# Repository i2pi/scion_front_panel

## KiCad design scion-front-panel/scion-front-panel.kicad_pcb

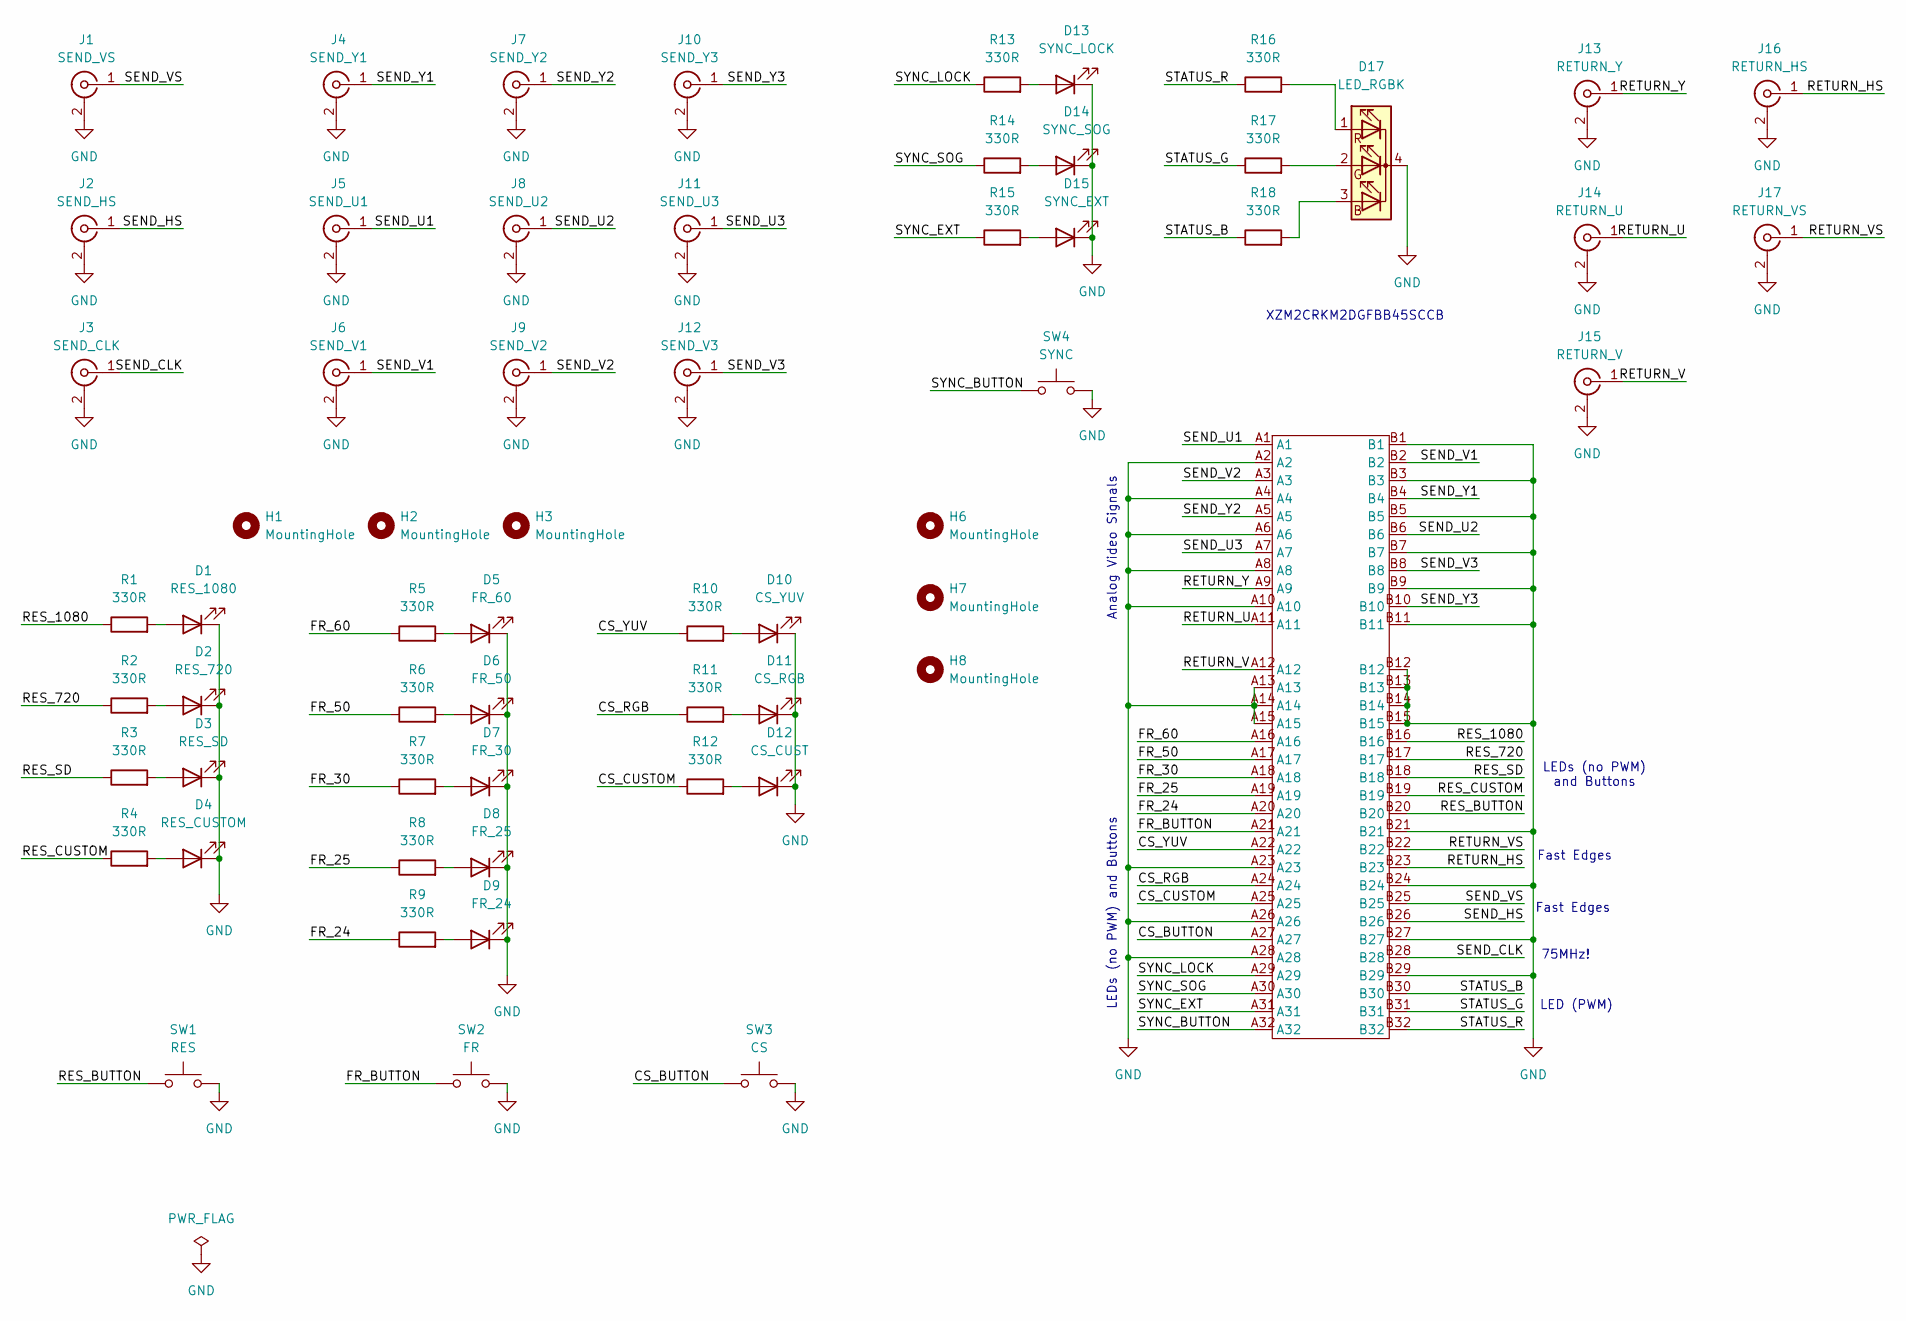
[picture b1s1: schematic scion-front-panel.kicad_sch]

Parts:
D1: RES_1080; LED_0805_2012Metric
D2: RES_720; LED_0805_2012Metric
D3: RES_SD; LED_0805_2012Metric
D4: RES_CUSTOM; LED_0805_2012Metric
D5: FR_60; LED_0805_2012Metric
D6: FR_50; LED_0805_2012Metric
D7: FR_30; LED_0805_2012Metric
D8: FR_25; LED_0805_2012Metric
D9: FR_24; LED_0805_2012Metric
D10: CS_YUV; LED_0805_2012Metric
D11: CS_RGB; LED_0805_2012Metric
D12: CS_CUST; LED_0805_2012Metric
D13: SYNC_LOCK; LED_0805_2012Metric
D14: SYNC_SOG; LED_0805_2012Metric
D15: SYNC_EXT; LED_0805_2012Metric
D17: LED_RGBK; LED_RGB_Wuerth-PLCC4_3.2x2.8mm_150141M173100
H1, H2, H3, H6, H7, H8: MountingHole; MountingHole_2.2mm_M2
J1: SEND_VS; SAMTEC_DIN7A-J-P-GF-ST-TH1
J2: SEND_HS; SAMTEC_DIN7A-J-P-GF-ST-TH1
J3: SEND_CLK; SAMTEC_DIN7A-J-P-GF-ST-TH1
J4: SEND_Y1; SAMTEC_DIN7A-J-P-GF-ST-TH1
J5: SEND_U1; SAMTEC_DIN7A-J-P-GF-ST-TH1
J6: SEND_V1; SAMTEC_DIN7A-J-P-GF-ST-TH1
J7: SEND_Y2; SAMTEC_DIN7A-J-P-GF-ST-TH1
J8: SEND_U2; SAMTEC_DIN7A-J-P-GF-ST-TH1
J9: SEND_V2; SAMTEC_DIN7A-J-P-GF-ST-TH1
J10: SEND_Y3; SAMTEC_DIN7A-J-P-GF-ST-TH1
J11: SEND_U3; SAMTEC_DIN7A-J-P-GF-ST-TH1
J12: SEND_V3; SAMTEC_DIN7A-J-P-GF-ST-TH1
J13: RETURN_Y; SAMTEC_DIN7A-J-P-GF-ST-TH1
J14: RETURN_U; SAMTEC_DIN7A-J-P-GF-ST-TH1
J15: RETURN_V; SAMTEC_DIN7A-J-P-GF-ST-TH1
J16: RETURN_HS; SAMTEC_DIN7A-J-P-GF-ST-TH1
J17: RETURN_VS; SAMTEC_DIN7A-J-P-GF-ST-TH1
J18: Bus_PCI_Express_x4-SCION; BUS_PCIexpress_x4
R1, R2, R3, R4, R5, R6, R7, R8, R9, R10, R11, R12, R13, R14, R15, R16, R17, R18: 330R; R_0402_1005Metric
SW1: RES; SW_SPST_Omron_B3FS-105xP
SW2: FR; SW_SPST_Omron_B3FS-105xP
SW3: CS; SW_SPST_Omron_B3FS-105xP
SW4: SYNC; SW_SPST_Omron_B3FS-105xP

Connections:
/CS_BUTTON: J18.A27, SW3.1
/CS_CUSTOM: J18.A25, R12.1
/CS_RGB: J18.A24, R11.1
/CS_YUV: J18.A22, R10.1
/FR_24: J18.A20, R9.1
/FR_25: J18.A19, R8.1
/FR_30: J18.A18, R7.1
/FR_50: J18.A17, R6.1
/FR_60: J18.A16, R5.1
/FR_BUTTON: J18.A21, SW2.1
/RES_720: J18.B17, R2.1
/RES_1080: J18.B16, R1.1
/RES_BUTTON: J18.B20, SW1.1
/RES_CUSTOM: J18.B19, R4.1
/RES_SD: J18.B18, R3.1
/RETURN_HS: J16.1 (In), J18.B23
/RETURN_U: J14.1 (In), J18.A11
/RETURN_V: J15.1 (In), J18.A12
/RETURN_VS: J17.1 (In), J18.B22
/RETURN_Y: J13.1 (In), J18.A9
/SEND_CLK: J3.1 (In), J18.B28
/SEND_HS: J2.1 (In), J18.B26
/SEND_U1: J5.1 (In), J18.A1
/SEND_U2: J8.1 (In), J18.B6
/SEND_U3: J11.1 (In), J18.A7
/SEND_V1: J6.1 (In), J18.B2
/SEND_V2: J9.1 (In), J18.A3
/SEND_V3: J12.1 (In), J18.B8
/SEND_VS: J1.1 (In), J18.B25
/SEND_Y1: J4.1 (In), J18.B4
/SEND_Y2: J7.1 (In), J18.A5
/SEND_Y3: J10.1 (In), J18.B10
/STATUS_B: J18.B30, R18.1
/STATUS_G: J18.B31, R17.1
/STATUS_R: J18.B32, R16.1
/SYNC_BUTTON: J18.A32, SW4.1
/SYNC_EXT: J18.A31, R15.1
/SYNC_LOCK: J18.A29, R13.1
/SYNC_SOG: J18.A30, R14.1
GND: D1.1 (K), D2.1 (K), D3.1 (K), D4.1 (K), D5.1 (K), D6.1 (K), D7.1 (K), D8.1 (K), D9.1 (K), D10.1 (K), D11.1 (K), D12.1 (K), D13.1 (K), D14.1 (K), D15.1 (K), D17.4 (K), J1.2 (Ext), J2.2 (Ext), J3.2 (Ext), J4.2 (Ext), J5.2 (Ext), J6.2 (Ext), J7.2 (Ext), J8.2 (Ext), J9.2 (Ext), J10.2 (Ext), J11.2 (Ext), J12.2 (Ext), J13.2 (Ext), J14.2 (Ext), J15.2 (Ext), J16.2 (Ext), J17.2 (Ext), J18.A2, J18.A4, J18.A6, J18.A8, J18.A10, J18.A13, J18.A14, J18.A15, J18.A23, J18.A26, J18.A28, J18.B1, J18.B3, J18.B5, J18.B7, J18.B9, J18.B11, J18.B12, J18.B13, J18.B14, J18.B15, J18.B21, J18.B24, J18.B27, J18.B29, SW1.2, SW2.2, SW3.2, SW4.2
unnamed: D1.2 (A), R1.2
unnamed: D2.2 (A), R2.2
unnamed: D3.2 (A), R3.2
unnamed: D4.2 (A), R4.2
unnamed: D5.2 (A), R5.2
unnamed: D6.2 (A), R6.2
unnamed: D7.2 (A), R7.2
unnamed: D8.2 (A), R8.2
unnamed: D9.2 (A), R9.2
unnamed: D10.2 (A), R10.2
unnamed: D11.2 (A), R11.2
unnamed: D12.2 (A), R12.2
unnamed: D13.2 (A), R13.2
unnamed: D14.2 (A), R14.2
unnamed: D15.2 (A), R15.2
unnamed: D17.3 (BA), R18.2
unnamed: D17.2 (GA), R17.2
unnamed: D17.1 (RA), R16.2

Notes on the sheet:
75MHz!
Analog Video Signals
LEDs (no PWM) and Buttons
LED (PWM)
XZM2CRKM2DGFBB45SCCB
LEDs (no PWM) and Buttons
Fast Edges

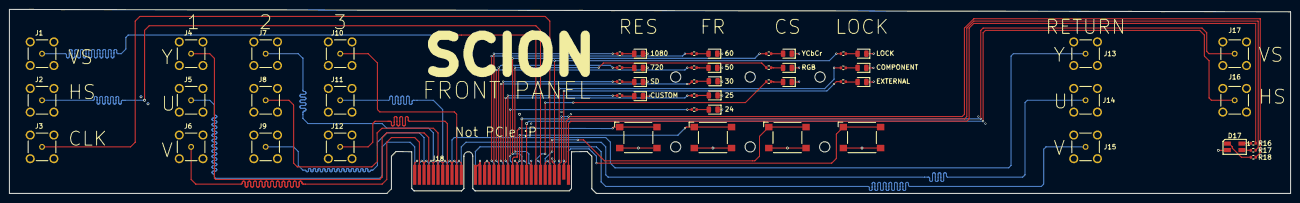
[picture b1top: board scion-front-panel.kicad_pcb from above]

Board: 4 copper layers, 274.9 x 39.5 mm, 62 parts (0 on the bottom side), 58 nets.

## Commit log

2025-07-20 frist
2025-07-20 getting jiggy with it
2025-07-20 neater squiggles
2025-07-20 fixed LED alignment and gnd filled zone
2025-07-20 neat
